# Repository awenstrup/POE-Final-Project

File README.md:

# POE-Final-Project

### Minimum Viable Product
Our MVP is to a build an intelligent, battery powered four wheel vehicle with remote data acquisition capabilities and sensor informed driving characteristics. Some stretch goals of ours are to include an intelligent drive algorithm with variable torque delivery for our wheels, self driving capabilities, aerodynamic features, video recording ability, and real time data plotting. We aim to prioritize robust, informed design and reliability. 

This project is a work in progress, with an estimated completion date in early December. Stay tuned for more updates.

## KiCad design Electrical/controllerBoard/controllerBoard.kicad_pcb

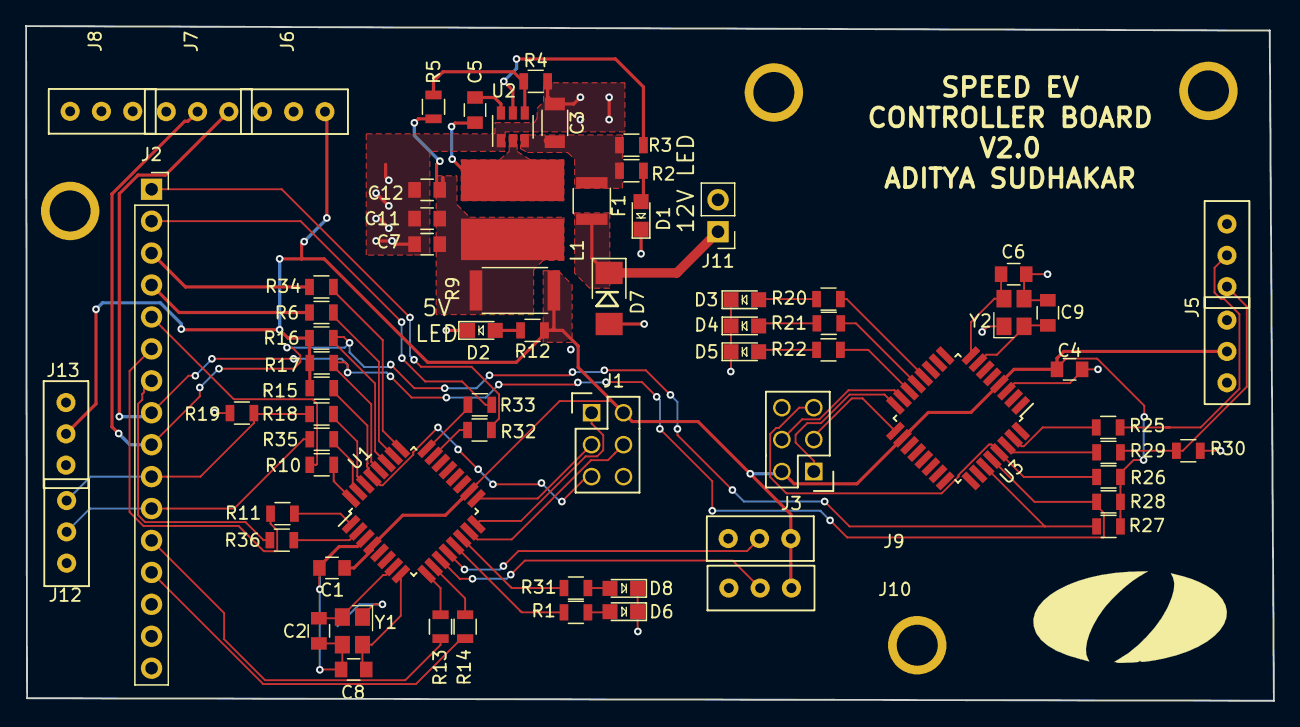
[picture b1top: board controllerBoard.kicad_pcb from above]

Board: 2 copper layers, 99.3 x 53.7 mm, 71 parts (0 on the bottom side), 63 nets.

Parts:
C1, C4, C5, C12: C_0.1uF; C_0805_OEM
C2, C6, C8, C9: C_30pF; C_0805_OEM
C3: C_22uF; C_1206_OEM
C7: C_47uF; C_0805_OEM
C11: C_1uF; C_0805_OEM
D1, D2, D3, D4, D5, D6, D8: LED_0805; LED_0805_OEM
D7: D_Zener_18V; DO-214AA
F1: 500mA; Fuse_1210
J1, J3: CONN_02X03; Pin_Header_Straight_2x03
J2: 0.1in_Female_Socket_01x16; PinSocket_1x16_P2.54mm_Vertical
J4, J5, J6, J7, J8, J9, J10, J12, J13: CONN_01X03; MHSS1105
J11: CONN_01x02; PinHeader_1x02_P2.54mm_Vertical
L1: L_4.7uH; 4.7uH_Inductor_OEM
R1, R12, R20, R21, R22, R31: R_200; R_0805_OEM
R2: R_1k; R_0805_OEM
R3, R4: R_10k; R_0805_OEM
R5: R_51.1k; R_0805_OEM
R6, R10, R11, R13, R14, R25, R32, R33, R34, R35, R36: R_0; R_0805_OEM
R9: R_0_Jumper; R_2512_OEM
R15, R16, R17, R26, R27, R28: R_10K; R_0805_OEM
R18, R29: R_1K; R_0805_OEM
R19, R30: R_2.2K; R_0805_OEM
U1, U3: ATmega328P-AU; TQFP-32_7x7mm_P0.8mm
U2: TPS561201; SOT-23-6_OEM
Y1, Y2: Crystal_SMD; Crystal_SMD_FA238

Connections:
+9V: D7.1, F1.1, J11.1
/12V_Fused: C3.1, F1.2, R2.1, R3.1, U2.3
/IO1: J2.1, R32.1
/IO2: J2.2, R33.1
/IO3: J2.3, R34.1
/IO4: J2.4, R6.1
/IO5: J2.5, R10.1
/IO6: J2.6, R11.1
/IO7: J2.7, R36.1
/IO8: J2.12, R13.1
/IO9: J2.13, R14.1
/MISO: J1.1, U1.16
/MISO2: J3.1, U3.16
/MOSI: J1.4, U1.15
/MOSI2: J3.4, U3.15
/RESET: J1.5, R15.2, U1.29
/RESET2: J3.5, R26.2, U3.29
/RX: J2.10, J12.3, R18.1, R19.2
/RX2: J4.3, R29.1, R30.2
/SCK: J1.3, U1.17
/SCK2: J3.3, U3.17
/SCL: J2.8, J7.1, R17.2, R28.2, U1.28, U3.28
/SDA: J2.9, J7.2, R16.2, R27.2, U1.27, U3.27
/STEERING_SENSE: J10.2, U1.11
/THROTTLE_SENSE: J9.2, U1.12
/TX: J2.11, J12.2, R35.1
/TX2: J4.2, R25.1
/XTAL1: C2.1, U1.7, Y1.1
/XTAL2: C8.1, U1.8, Y1.3
/XTAL3: C9.1, U3.7, Y2.1
/XTAL4: C6.1, U3.8, Y2.3
GND: C1.2, C2.2, C3.2, C4.2, C6.2, C7.2, C8.2, C9.2, C11.2, C12.2, D1.1, D2.1, D3.1, D4.1, D5.1, D6.1, D7.2, D8.1, J1.6, J3.6, J5.1, J6.3, J9.3, J10.3, J11.2, J13.1, R4.2, R19.1, R30.1, U1.3, U2.1, U3.3, Y1.2, Y1.4, Y2.2, Y2.4
unnamed: C5.1, U2.6
unnamed: C5.2, L1.1, U2.2
unnamed: C7.1, C11.1, C12.1, L1.2, R5.2, R9.2
unnamed: D1.2, R2.2
unnamed: D2.2, R12.2
unnamed: D3.2, R20.1
unnamed: D4.2, R21.1
unnamed: D5.2, R22.1
unnamed: D6.2, R1.1
unnamed: D8.2, R31.1
unnamed: R1.2, U1.13
unnamed: R3.2, U2.5
unnamed: R4.1, R5.1, U2.4
unnamed: R6.2, U1.26
unnamed: R10.2, U1.32
unnamed: R11.2, U1.1
unnamed: R13.2, U1.9
unnamed: R14.2, U1.10
unnamed: R18.2, U1.30
unnamed: R20.2, U3.12
unnamed: R21.2, U3.13
unnamed: R22.2, U3.14
unnamed: R25.2, U3.31
unnamed: R29.2, U3.30
unnamed: R31.2, U1.14
unnamed: R32.2, U1.23
unnamed: R33.2, U1.24
unnamed: R34.2, U1.25
unnamed: R35.2, U1.31
unnamed: R36.2, U1.2
VCC: C1.1, C4.1, J1.2, J3.2, J5.2, J6.1, J9.1, J10.1, J13.2, R9.1, R12.1, R15.1, R16.1, R17.1, R26.1, R27.1, R28.1, U1.4, U1.18, U3.4, U3.18

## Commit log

2019-10-15 Created subteam folders
2019-10-21 Added code to read and print PWM from RF reciever (have not set pins yet)
2019-10-22 Added structure for motor control to script; still not mapping raw reciever input to output
2019-10-24 Wrote code to drive sketch model car; have not tested yet; does not steer
2019-10-24 Working code for car rev0 (steering and forward movement via remote control)
2019-10-24 Cleaned up rev0 code, added comments
2019-10-29 First draft of throttle code with reverse, not tested
2019-10-29 Started adding interupts to replace pulseIn, not done yet
2019-11-01 Finished first draft of of new code (using interupts instead of pulseIn); does not work
2019-11-07 Continued work on interupts; timer working, PCINT not working as intended
2019-11-07 Very jank way to drive motor through ESC, plz fix
2019-11-07 Drive motors through ESCs; still jank, just forgot to save
2019-11-08 Swapped throttle pin to PCINT0 (interupt register 0); steering still in PCINT22 (interupt register 2)
2019-11-08 Enabled the correct pin change interupts, still have to write ISRs
2019-11-08 Setup ISRs for new PCINTs
2019-11-13 Checkpoint as of 11/13
2019-11-15 adding website boiler plate
2019-11-16 -Adding Controller board KiCAD project files
2019-11-17 Beggining of day, november 17 (began readapting to use pulseIn again, not finished)
2019-11-17 Got variable throttle output working
2019-11-17 pushing controller board files
2019-11-19 Final version trying to connect Arduino to ESC; ESC recognized something, but didn't work reliably
2019-11-19 First pass at variable steering output, not tested
2019-11-20 Dynamic steering works; tested and centered!
2019-11-20 Code successfully outputs accelerometer data to the *internet*
2019-11-21 Added calibration sketch; got throttle code working!
2019-11-21 It works!
2019-11-22 Working code; activating bluetooth disables motor control
2019-11-22 Working driving and bluetooth streaming, good code
2019-12-06 Working code as of 12/5
2019-12-11 Added variable steering assist through the controller
2019-12-13 updating website and controller board
2019-12-13 updated controller board
